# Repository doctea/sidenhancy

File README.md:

# sidenhancy

- Eurorack module based around the ARMSID SID chip clone
- Based around Atmega 1284p
 - oled display and rotary encoder options
 - CV inputs assignable to SID parameters
- Using [mymenu](https://github.com/doctea/mymenu) and [parameters](https://github.com/doctea/parameters)

## Hardware/PCB

- See [Wiring.md](Wiring.md) for pin wiring (unchecked / incomplete / untested!!)
- Note that **PCB FILES in pcb/ ARE NOT FINISHED, DO NOT USE THESE YET!!**

## Todo

- Parameters
  - Oscillator 1/root pitch
  - Oscillator 2 pitch
  - Oscillator 3 pitch
  - Oscillator 1 waveforms selectable 
  - Oscillator 2 waveforms selectable 
  - Oscillator 3 waveforms selectable 
  - Oscillator 1 Pulse width
  - Oscillator 2 Pulse width
  - Oscillator 3 Pulse width
  - Oscillator Detune
  - Chord
  - Filter on/off for oscillator 1
  - Filter on/off for oscillator 2
  - Filter on/off for oscillator 3
  - Filter modes LP / BP / HP
  - Filter cutoff
  - Pitch Quantization settings
- Use SID ADSR?
  - optional so module can just be used as an oscillator
  - otherwise have ADSR for each oscillator be configurable?
- ~~Menu system (using https://github.com/doctea/mymenu)~~
 - ~~Input via rotary encoder + buttons~~
   - (unreliably working with straight encoder)
   - ~~todo: i2c rotary encoder~~
 - ~~System to map assignable inputs to parameters~~
- ~~Display via i2c ss_oled~~
- CV inputs
  - Pitch
    - (working for 0-5v, quantised and not)
    - Make work with 2xPimoroni 24v ADS1015 breakouts
    - tuning / calibration functions
    - ~~three of them, one for each oscillator?~~
    - pitch modulation
    - portamento/glide
  - Filter cutoff
  - Assignable input?
- internal LFOs?
- MIDI input
- Circuit
  - Schematic
    - in progress in pcb/
  - PCB
    - in progress in pcb/
- Panel

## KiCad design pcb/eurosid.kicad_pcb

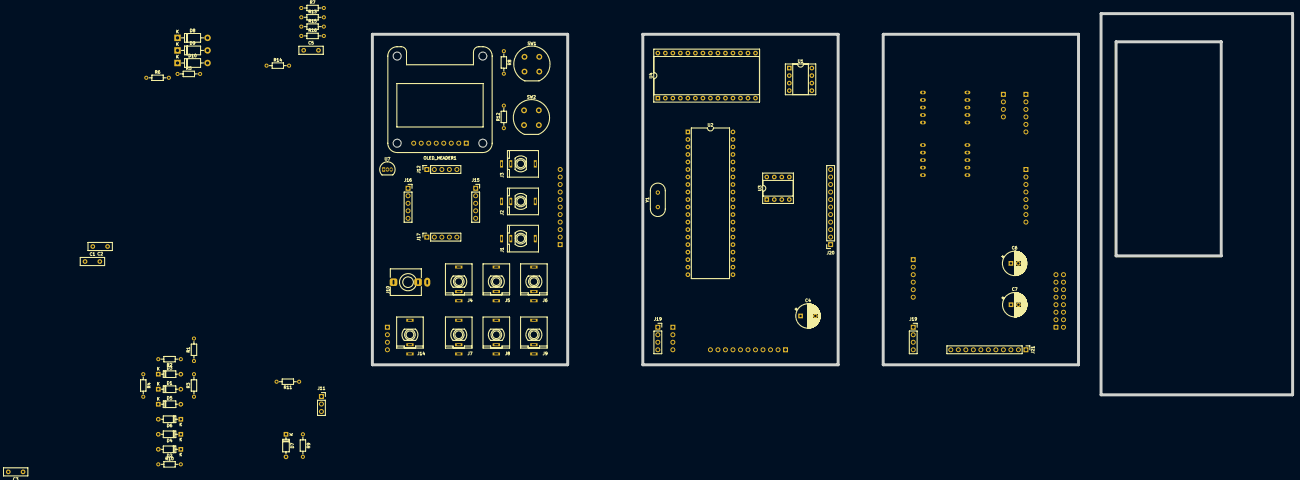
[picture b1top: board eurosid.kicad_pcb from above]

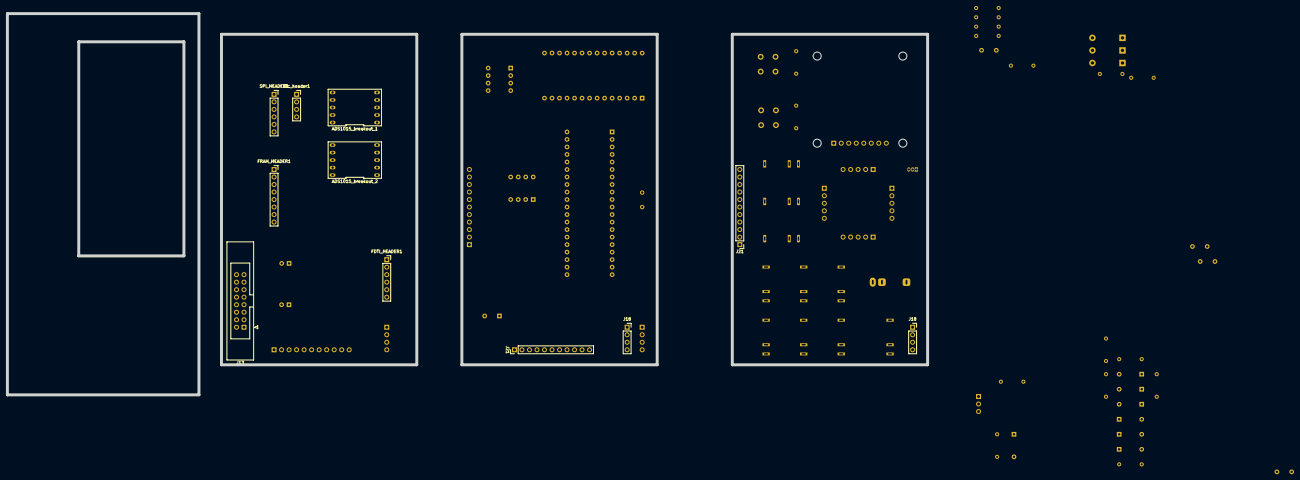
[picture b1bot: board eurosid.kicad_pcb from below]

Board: 2 copper layers, 311.1 x 128.9 mm, 73 parts (11 on the bottom side), 65 nets, no tracks yet.

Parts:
ADS1015_breakout_1: ADS1015_breakout
ADS1015_breakout_2: ADS1015_breakout_2; ADS1015_breakout
C1, C2: 22pf; C_Disc_D8.0mm_W2.5mm_P5.00mm
C3: 0.1uf; C_Disc_D8.0mm_W2.5mm_P5.00mm
C4: 1uf; CP_Radial_D8.0mm_P5.00mm
C5: 1nf; C_Disc_D8.0mm_W2.5mm_P5.00mm
C6, C7: CP; CP_Radial_D8.0mm_P2.50mm
D1, D2, D3, D4, D5, D6: D_Schottky; D_DO-35_SOD27_P7.62mm_Horizontal
D7: 1N4148; D_DO-35_SOD27_P7.62mm_Horizontal
D8, D9, D10: 1N5817; D_DO-41_SOD81_P10.16mm_Horizontal
FDTI_HEADER1: Conn_01x06_Female; PinSocket_1x06_P2.54mm_Vertical
FRAM_HEADER1: FRAM_Breakout_i2c_01x08; PinSocket_1x08_P2.54mm_Vertical
J1: Gate 1 In; thonkiconn_fuzzySi
J2: Gate 2 In; thonkiconn_fuzzySi
J3: Gate 3 In; thonkiconn_fuzzySi
J4: Input_Jack_A; thonkiconn_fuzzySi
J5: Input_Jack_B; thonkiconn_fuzzySi
J6: Input_Jack_C; thonkiconn_fuzzySi
J7: Input_Jack_D; thonkiconn_fuzzySi
J8: Input_Jack_E; thonkiconn_fuzzySi
J9: Input_Jack_F; thonkiconn_fuzzySi
J10: Stereo jack - MiDI TRS; Jack_3.5mm_QingPu_WQP-PJ366ST_Vertical
J11: MIDI IN Conn_01x03_Male; PinSocket_1x03_P2.54mm_Vertical
J12, J15, J16, J17: i2c encoder; PinSocket_1x05_P2.54mm_Vertical
J13: Euro power; IDC-Header_2x08_P2.54mm_Latch_Vertical
J14: Audio Out Jack; thonkiconn_fuzzySi
J18, J18#2, J19, J19#2: i2c_header_2; PinSocket_1x04_P2.54mm_Vertical
J20: Conn_01x11_Female; PinSocket_1x11_P2.54mm_Vertical
J21, J21#2, J21#3: Conn_01x11_Male; PinHeader_1x11_P2.54mm_Vertical
OLED_HEADER1: SSD1306_i2c_Oled_Conn; Adafruit_SSD1306
R1, R2, R3, R4, R5, R6, R14: 10k; R_Axial_DIN0204_L3.6mm_D1.6mm_P7.62mm_Horizontal
R7: 100k; R_Axial_DIN0204_L3.6mm_D1.6mm_P7.62mm_Horizontal
R8, R12: R; R_Axial_DIN0204_L3.6mm_D1.6mm_P7.62mm_Horizontal
R9, R11: 220R; R_Axial_DIN0204_L3.6mm_D1.6mm_P7.62mm_Horizontal
R10: 4.7K; R_Axial_DIN0204_L3.6mm_D1.6mm_P7.62mm_Horizontal
R13: 220k; R_Axial_DIN0204_L3.6mm_D1.6mm_P7.62mm_Horizontal
R15, R16: 22; R_Axial_DIN0204_L3.6mm_D1.6mm_P7.62mm_Horizontal
SPI_HEADER1: Conn_01x06_Female; PinSocket_1x06_P2.54mm_Vertical
SW1, SW2: SW_Push_Dual; Push_E-Switch_KS01Q01
U1: 6N138; DIP-8_W7.62mm_Socket
U2: ATmega1284-PU; DIP-40_W15.24mm
U3: TL072; DIP-8_W7.62mm_Socket
U4: MOS6581_6582_8580SID; DIP-28_W15.24mm_Socket
U7: L78L33_TO92; TO-92_Inline
Y1: Crystal; Crystal_HC18-U_Vertical
i2c_header1: i2c_spare; PinSocket_1x04_P2.54mm_Vertical

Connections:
3.3v: OLED_HEADER1.1, U7.1
+5V: ADS1015_breakout_1.1, ADS1015_breakout_1.6, ADS1015_breakout_2.1, ADS1015_breakout_2.6, D1.1, D3.1, D5.1, D10.1, FDTI_HEADER1.4, FRAM_HEADER1.8, J12.2, J15.2, J16.2, J17.2, J18.4, J18#2.4, J19.4, J19#2.4, R4.1, R8.2, R11.2, R12.2, SPI_HEADER1.1, U1.8, U2.10, U2.30, U2.32, U4.25, U4.28, U7.3, i2c_header1.1
+12V: C7.1, R16.2, U3.8
-12V: C6.2, R15.2
BUTTON_A: R8.1, SW1.3, U2.29
BUTTON_B: R12.1, SW2.3, U2.28
GND: ADS1015_breakout_1.5, ADS1015_breakout_1.10, ADS1015_breakout_2.5, ADS1015_breakout_2.10, C1.1, C2.2, C5.1, C6.1, C7.2, D2.2, D4.2, D6.2, FDTI_HEADER1.6, FRAM_HEADER1.7, J1.1, J1.2, J2.1, J2.2, J3.1, J3.2, J4.1, J4.2, J5.1, J5.2, J6.1, J6.2, J7.1, J7.2, J8.1, J8.2, J9.1, J9.2, J10.S, J11.1, J12.1, J13.3, J13.4, J13.5, J13.6, J13.7, J13.8, J14.1, J14.2, J15.1, J16.1, J17.1, J18.3, J18#2.3, J19.3, J19#2.3, J20.11, J21.11, J21#2.11, J21#3.11, OLED_HEADER1.2, R5.1, R6.1, R7.2, R10.1, SPI_HEADER1.2, SW1.4, SW2.4, U1.5, U2.11, U2.31, U4.14, U7.2, i2c_header1.2
Gate_1_IN: J20.2, J21.2, J21#2.2, J21#3.2, R1.2, U2.25
Gate_2_IN: J20.3, J21.3, J21#2.3, J21#3.3, R2.2, U2.26
Gate_3_IN: J20.4, J21.4, J21#2.4, J21#3.4, R3.2, U2.27
INPUT_A: ADS1015_breakout_1.7, J4.3, J20.5, J21.5, J21#2.5, J21#3.5
INPUT_B: ADS1015_breakout_1.8, J5.3, J20.6, J21.6, J21#2.6, J21#3.6
INPUT_C: ADS1015_breakout_1.9, J6.3, J20.7, J21.7, J21#2.7, J21#3.7
INPUT_D: ADS1015_breakout_2.9, J7.3, J20.8, J21.8, J21#2.8, J21#3.8
INPUT_E: ADS1015_breakout_2.8, J8.3, J20.9, J21.9, J21#2.9, J21#3.9
INPUT_F: ADS1015_breakout_2.7, J9.3, J20.10, J21.10, J21#2.10, J21#3.10
JACK_OUT: J14.3, J20.1, J21.1, J21#2.1, J21#3.1, U3.6, U3.7
MIDI_ATMEGA_RX: R11.1, U1.6, U2.14
MIDI_TX: FDTI_HEADER1.2, U2.15
unnamed: C1.2, U2.13, Y1.2
unnamed: C2.1, U2.12, Y1.1
unnamed: C3.1, R4.2, U2.9
unnamed: C3.2, FDTI_HEADER1.1
unnamed: C4.2, R7.1, U3.3
unnamed: C5.2, R14.2, U3.5
unnamed: D1.2, D2.1, J1.3, R1.1
unnamed: D3.2, D4.1, J2.3, R2.1
unnamed: D5.2, D6.1, J3.3, R3.1
unnamed: D7.1, R9.1, U1.2
unnamed: D7.2, J10.T, J11.3, U1.3
unnamed: D8.1, J13.1, J13.2
unnamed: D8.2, R15.1
unnamed: D9.1, R16.1
unnamed: D9.2, J13.9, J13.10
unnamed: D10.2, J13.11, J13.12
unnamed: J10.R, J11.2, R9.2
unnamed: J13.13, J13.14
unnamed: J13.15, J13.16
unnamed: R10.2, U1.7
unnamed: R6.2, R13.1, U3.2
unnamed: R13.2, R14.1, U3.1
SID_A0: U2.16, U4.9
SID_A1: U2.17, U4.10
SID_A2: U2.20, U4.11
SID_A3: U2.21, U4.12
SID_A4: U2.24, U4.13
SID_AUDIO_OUT: C4.1, R5.2, U4.27
SID_CLOCK: U2.19, U4.6
SID_CS: U2.2, U4.8
SID_D0: U2.33, U4.15
SID_D1: U2.34, U4.16
SID_D2: U2.35, U4.17
SID_D3: U2.36, U4.18
SID_D4: U2.37, U4.19
SID_D5: U2.38, U4.20
SID_D6: U2.39, U4.21
SID_D7: U2.40, U4.22
SID_RESET: U2.4, U4.5
SID_RW: U2.1, U4.7
SPI_MISO: SPI_HEADER1.4, U2.7
SPI_MOSI: SPI_HEADER1.5, U2.6
SPI_SCK: SPI_HEADER1.3, U2.8
SPI_SS: SPI_HEADER1.6, U2.5
i2c_SCL: ADS1015_breakout_1.3, ADS1015_breakout_2.3, FRAM_HEADER1.5, J12.4, J15.4, J16.4, J17.4, J18.2, J18#2.2, J19.2, J19#2.2, OLED_HEADER1.3, U2.22, i2c_header1.3
i2c_SDA: ADS1015_breakout_1.2, ADS1015_breakout_2.2, FRAM_HEADER1.4, J12.3, J15.3, J16.3, J17.3, J18.1, J18#2.1, J19.1, J19#2.1, OLED_HEADER1.4, U2.23, i2c_header1.4

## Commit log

2022-05-20 first commit of proof of concept with CV control of pitch
2022-05-21 ok, some debug stuff over serial, seems to basically be working in all instances now?
2022-05-21 working screen
2022-05-22 screen stuff moved to external library..! compiles, but doesn't run / crashes
2022-05-22 compiles, runs and screen initialises!
2022-05-22 compiles, runs, doesnt crash!
2022-05-22 works !
2022-05-22 fixed encoder pinout ..
2022-05-22 filter cutoff control via menu
2022-05-26 largely working with currenct version of the mymenu library!
2022-05-28 this build doesnt crash (doesnt work properly either tho, can only read from first ADC?)
2022-05-28 ok 2x inputs working, pulsewidth modulation!
2022-05-29 pulse width modulation on second cv input! seem to be running outta RAM though, had to wrap all strings with F()s to stop it from crashing when added more menu items
2022-06-05 ... with i2cencoder, but very unreliable, going to revert to previous versions to try and and work out why its crashing on start so frequently now
2022-06-05 seems to not crashy anymore? some weirdness going on with menu display tho
2022-06-05 remove unlabelled debug
2022-06-05 pulse width modulation kinda works. now gonna try implementing generic Parameter stuff
2022-06-06 builds against parameters library (but probably does not work)
2022-06-06 compiles + runs but doesnt work as intended still
2022-06-06 pitch is working with corresponding version of parameter library!
2022-06-06 pulse width modulation kinda working too
2022-06-06 powerloss commit?
2022-06-06 menu item displaying % for Parameters
2022-06-06 alright, multiple parameters added with relative ease, inverting etc
2022-06-07 menu for selecting mappings basically works (messy display tho)
2022-06-07 menu display working ok, something weird going on tho i think still with repo maybe?
2022-06-07 alrighty, parameter formatted values being shown -- had to make it static in function with const return type?
2022-06-07 display info about selected parameterinput
2022-06-08 add 'None' option to selector
2022-06-08 move the ParameterSelectorControl into the Parameter library
2022-06-08 minor move of menu display mode setting before adding menu items - in case we need to know the mode at the point of adding in future
2022-06-11 don't specify types of Parameter when creating ParameterInputs; vibrato kinda working
2022-06-11 pitch tracking working again
2022-06-11 parameters automatically added
2022-06-12 sort of working toggle items for enabling waveforms, but not quite working. significant changes so doing in separate branch as may want to revert
2022-06-12 add more per-voice parameters
2022-06-13 per-voice frequency multiplier and extra inputs
2022-06-13 set up initial state of parameters+controls
2022-06-13 saves parameter info to fram; doesn't load it back in yet tho
2022-06-14 nonworking? reload code..
2022-06-14 allow to enable/disable storage
2022-06-14 bad merge
2022-06-16 save / loading of state works !
2022-07-09 filters and osc modes now largely work from menus, still some oddities though (noise osc worked once but not since?)
2022-07-09 use refactored VoltageSource stuff
2022-07-09 remove some old cruft, configurable option to restore parameterinput inverted+unipolar setting
2022-07-09 config to enable/disable two ADCs, dynamic creation of ParameterInputs from VoltageSources
2022-07-27 starting to document wiring...
2022-07-27 added SID pinout
2022-07-28 commit progress on schematic
2022-07-31 tracked hardware
2022-07-31 compiles against v0.0.3 of parameters library; but my i2c has stopped working(?) so dont know if working properly..
2022-07-31 unsure if this is needed
2022-08-02 slightly updated
2022-08-05 better separation of i2c configs so that easier to debug. change correction values to be more accurate to current situation
2022-08-30 moved Wiring.md into correct place; this version compiles and runs on my breadboard..
2022-08-30 proposed rearrangement...
2022-08-30 added ftdi header
2022-08-30 realigned
2022-08-30 realigned again
